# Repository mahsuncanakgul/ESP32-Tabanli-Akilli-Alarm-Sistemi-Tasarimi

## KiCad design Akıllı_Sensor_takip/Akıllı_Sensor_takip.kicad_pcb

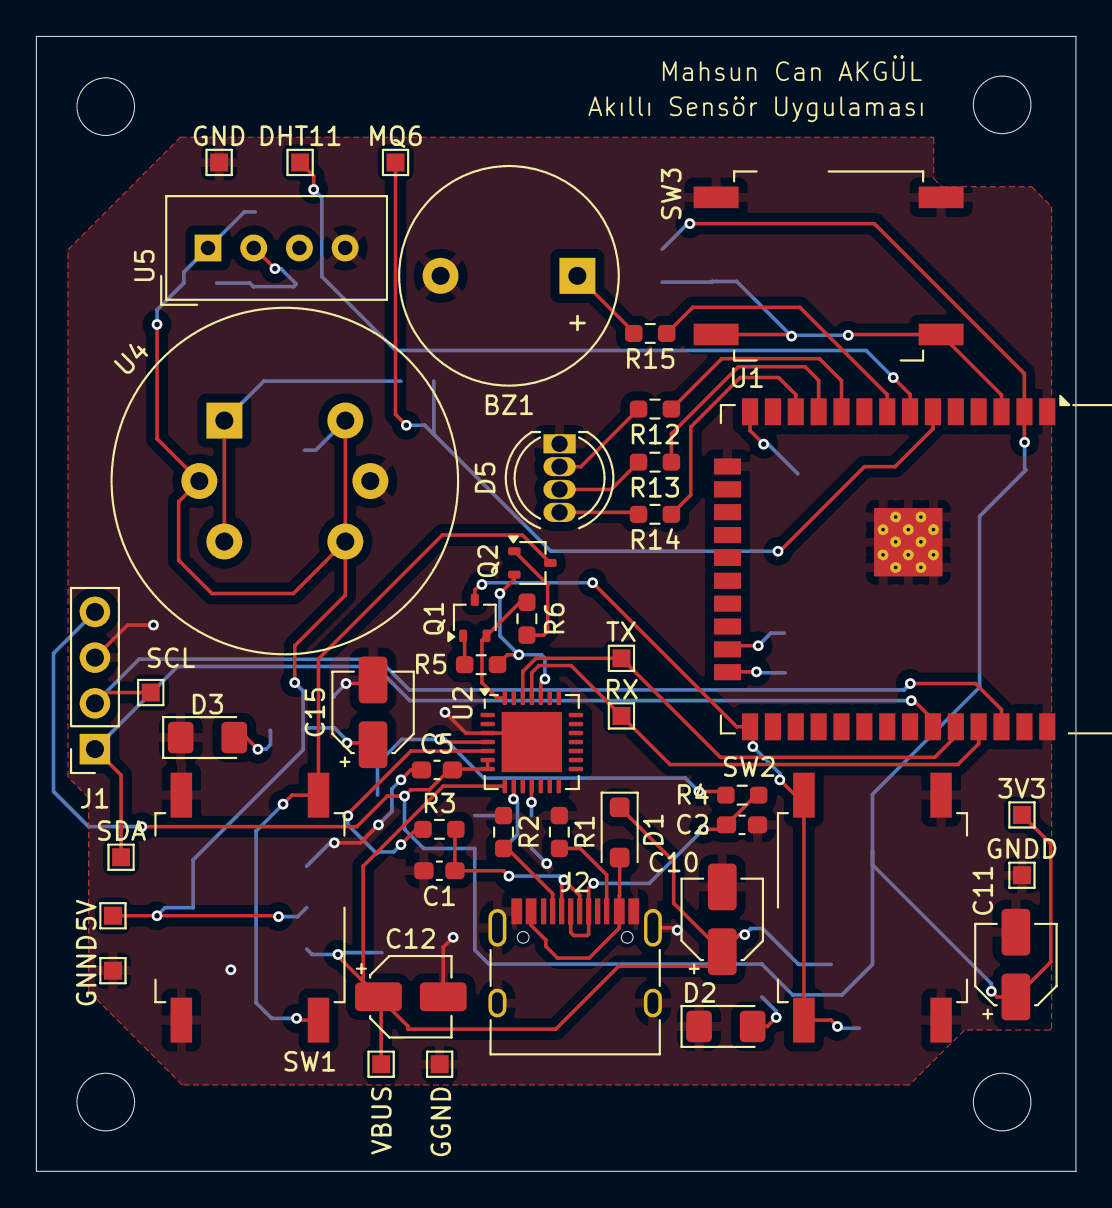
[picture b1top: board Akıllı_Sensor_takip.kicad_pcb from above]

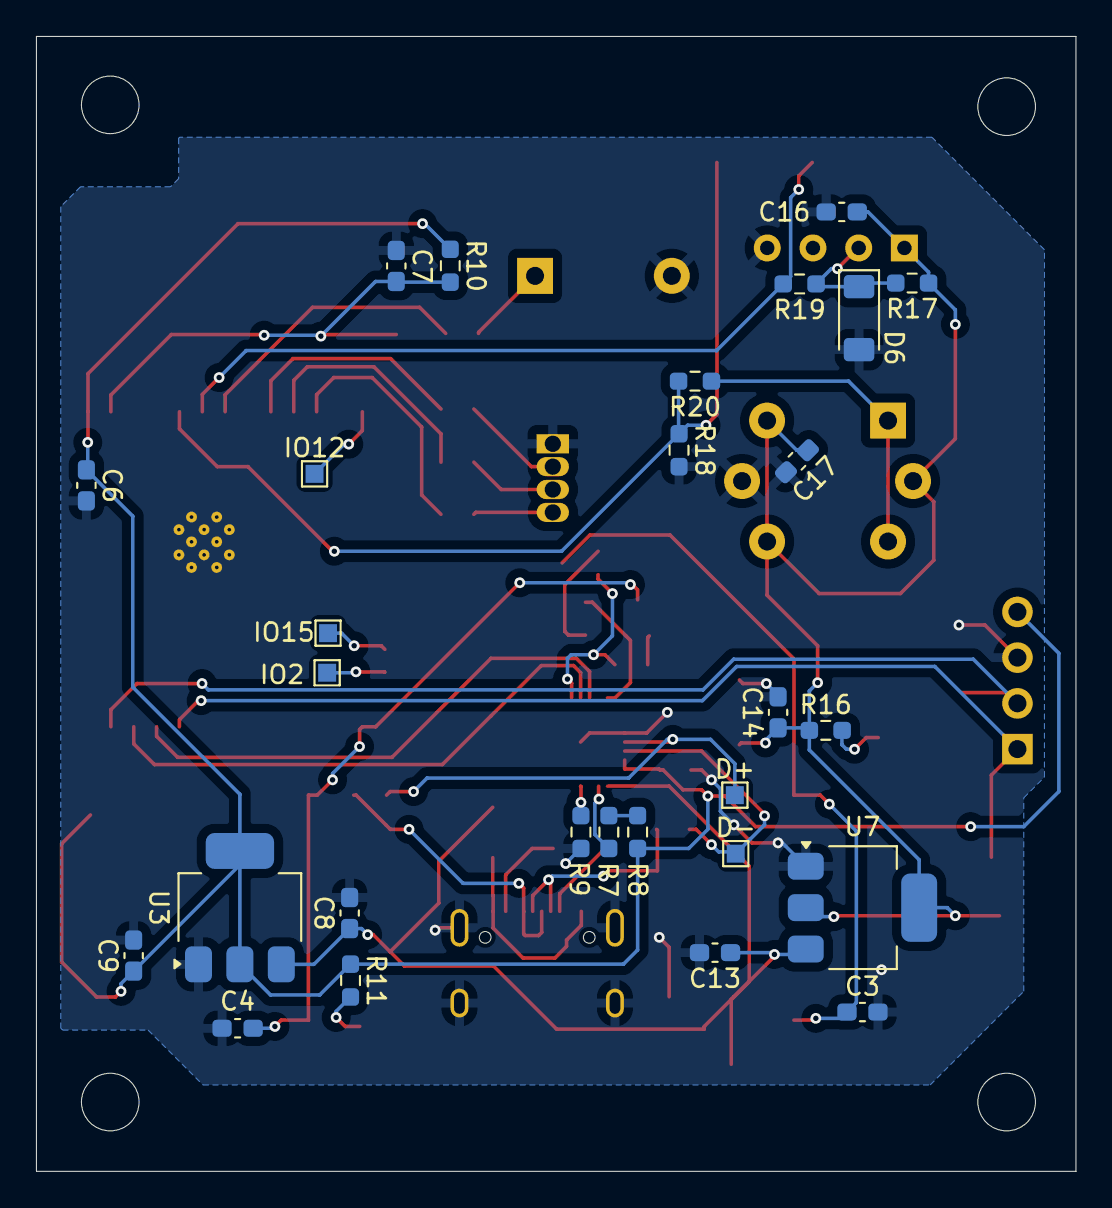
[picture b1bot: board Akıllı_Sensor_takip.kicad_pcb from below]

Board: 2 copper layers, 57.7 x 63.1 mm, 78 parts (28 on the bottom side), 42 nets.

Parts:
3V3, 5V: TestPoint; TestPoint_Pad_1.0x1.0mm
BZ1: Buzzer; Buzzer_12x9.5RM7.6
C1, C2: 47pF; C_0603_1608Metric_Pad1.08x0.95mm_HandSolder
C3, C4, C5, C6, C7, C8, C9, C13, C14, C16, C17: 100nF; C_0603_1608Metric_Pad1.08x0.95mm_HandSolder
C10, C11, C12, C15: 1uF; CP_Elec_4x5.3
D1: MBR1020VL; D_SOD-123F
D2: GREEN; LED_1206_3216Metric_Pad1.42x1.75mm_HandSolder
D3: BLUE; LED_1206_3216Metric_Pad1.42x1.75mm_HandSolder
D5: LED_KRGB; LED_D5.0mm-4_RGB
D6: BZV55B3V6; D_MiniMELF
D+: TestPoint; TestPoint_Pad_1.0x1.0mm
D-: TestPoint; TestPoint_Pad_1.0x1.0mm
DHT11: TestPoint; TestPoint_Pad_1.0x1.0mm
GGND: TestPoint; TestPoint_Pad_1.0x1.0mm
GND: TestPoint; TestPoint_Pad_1.0x1.0mm
GNDD: TestPoint; TestPoint_Pad_1.0x1.0mm
GNND: TestPoint; TestPoint_Pad_1.0x1.0mm
H1, H2, H3, H4: MountingHole; MountingHole_3.2mm_M3
IO2, IO12, IO15: TestPoint; TestPoint_Pad_1.0x1.0mm
J1: OLED; PinSocket_1x04_P2.54mm_Vertical
J2: USB_C_Receptacle_USB2.0_16P; USB_C_Receptacle_HRO_TYPE-C-31-M-12
MQ6: TestPoint; TestPoint_Pad_1.0x1.0mm
Q1, Q2: 2SC4213; SOT-323_SC-70
R1, R2: 5.1K; R_0603_1608Metric_Pad0.98x0.95mm_HandSolder
R3, R4: 27R; R_0603_1608Metric_Pad0.98x0.95mm_HandSolder
R5, R6, R9, R10, R18, R19: 10K; R_0603_1608Metric_Pad0.98x0.95mm_HandSolder
R7, R8: 1K; R_0603_1608Metric_Pad0.98x0.95mm_HandSolder
R11, R16: 330; R_0603_1608Metric_Pad0.98x0.95mm_HandSolder
R12, R13, R14, R15: 330R; R_0603_1608Metric_Pad0.98x0.95mm_HandSolder
R17: 4.7K; R_0603_1608Metric_Pad0.98x0.95mm_HandSolder
R20: 20K; R_0603_1608Metric_Pad0.98x0.95mm_HandSolder
RX: TestPoint; TestPoint_Pad_1.0x1.0mm
SCL: TestPoint; TestPoint_Pad_1.0x1.0mm
SDA: TestPoint; TestPoint_Pad_1.0x1.0mm
SW1, SW2, SW3: SW_MEC_5E; SW_MEC_5GSH9
TX: TestPoint; TestPoint_Pad_1.0x1.0mm
U1: ESP32-WROOM-32D
U2: CP2102N-Axx-xQFN28; QFN-28-1EP_5x5mm_P0.5mm_EP3.35x3.35mm
U3: AMS1117-3.3; SOT-223-3_TabPin2
U4: MQ-6
U5: DHT11; Aosong_DHT11_5.5x12.0_P2.54mm
U7: AMS1117-5.0; SOT-223-3_TabPin2
VBUS: TestPoint; TestPoint_Pad_1.0x1.0mm

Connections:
+3.3V: 3V3.1, C5.2, C6.1, C9.1, C11.1, J1.4, R8.1, R10.1, R11.1, U1.2 (VDD), U2.6 (VDD), U2.7 (VREGIN), U3.2 (VO)
+5V: 5V.1, C14.1, C15.1, C16.1, C17.1, R16.1, R17.1, U4.2 (VH+), U4.4 (A2), U4.6 (A1), U5.1 (VDD), U7.2 (VO)
BLUE: R14.1, U1.12 (IO27)
BUZZER: R15.1, U1.8 (IO32)
D+: D+.1, R4.1, U2.4 (D+)
D-: D-.1, R3.1, U2.5 (D-)
DHT11: DHT11.1, R19.2, U1.7 (IO35)
DTR: Q1.2 (E), R6.2, U2.28 (~DTR)
EN: C3.1, Q2.3 (C), SW1.1, SW1.2
GND: BZ1.2 (-), C1.2, C2.2, C3.2, C4.2, C5.1, C6.2, C7.1, C8.2, C9.2, C10.2, C11.2, C12.2, C13.2, C14.2, C15.2, C16.2, C17.2, D2.1 (K), D3.1 (K), D5.1 (K), D6.2 (A), GGND.1, GND.1, GNDD.1, GNND.1, J1.3, J2.A1 (GND), J2.A12 (GND), J2.B1 (GND), J2.B12 (GND), J2.S1 (SHIELD), R1.1, R2.1, R9.2, R18.2, SW1.3 (K), SW1.4 (A), SW2.3 (K), SW2.4 (A), SW3.1, SW3.2, U1.1 (GND), U1.15 (GND), U1.38 (GND), U1.39 (GND), U2.3 (GND), U2.29 (GND), U3.1 (GND), U4.5 (VH-), U5.4 (GND), U7.1 (GND)
GREEN: R13.1, U1.11 (IO26)
IO0: C4.1, Q1.3 (C), SW2.1, SW2.2, U1.25 (IO0)
IO2: IO2.1, U1.24 (IO2)
IO12: IO12.1, U1.14 (IO12)
IO15: IO15.1, U1.23 (IO15)
MQ6: MQ6.1, R18.1, R20.2, U1.6 (IO34)
unnamed: BZ1.1 (+), R15.2
unnamed: C1.1, J2.A7 (D-), J2.B7 (D-), R3.2
unnamed: C2.1, J2.A6 (D+), J2.B6 (D+), R4.2
unnamed: D1.2 (A), J2.A4 (VBUS), J2.A9 (VBUS), J2.B4 (VBUS), J2.B9 (VBUS)
unnamed: D2.2 (A), R11.2
unnamed: D3.2 (A), R16.2
unnamed: D5.4 (BA), R14.2
unnamed: D5.3 (GA), R13.2
unnamed: D5.2 (RA), R12.2
unnamed: D6.1 (K), R17.2, R19.1, U5.2 (DATA)
unnamed: J2.A5 (CC1), R2.2
unnamed: J2.B5 (CC2), R1.2
unnamed: Q1.1 (B), R5.1
unnamed: Q2.1 (B), R6.1
unnamed: R7.1, R8.2
unnamed: C7.2, R10.2, SW3.3 (K), SW3.4 (A), U1.3 (EN)
unnamed: R7.2, U2.9 (~RST)
unnamed: R9.1, U2.11 (~SUSPEND)
unnamed: R20.1, U4.1 (B1), U4.3 (B2)
OLED_SCL: J1.2, SCL.1, U1.36 (IO22)
OLED_SDA: J1.1, SDA.1, U1.33 (IO21)
RED: R12.1, U1.10 (IO25)
RTS: Q2.2 (E), R5.2, U2.24 (~RTS)
RX: RX.1, U1.35 (TXD0/IO1), U2.25 (RXD)
TX: TX.1, U1.34 (RXD0/IO3), U2.26 (TXD)
VBUS: C8.1, C10.1, C12.1, C13.1, D1.1 (K), U2.8 (VBUS), U3.3 (VI), U7.3 (VI), VBUS.1

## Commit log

2025-09-25 ESP32 Tabali Akilli Alarm Sistemi
    Bu projede, ESP32 kullanılarak ortamın sıcaklık, nem ve gaz değerleri ölçülecektir. Toplanan veriler, internet üzerinden kullanıcıya iletilecek ve böylece kullanıcı ortamda olmasa bile güncel durumu 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
